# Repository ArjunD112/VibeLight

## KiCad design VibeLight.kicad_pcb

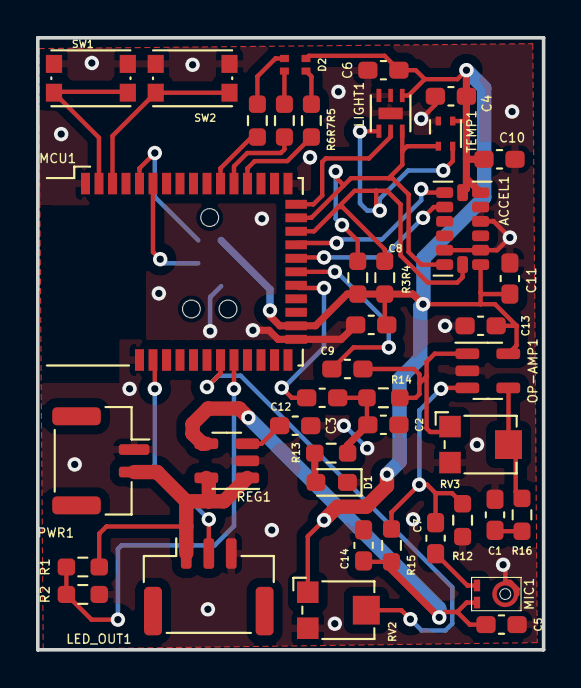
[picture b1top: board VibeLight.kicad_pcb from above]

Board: 2 copper layers, 28.1 x 34.0 mm, 42 parts (1 on the bottom side), 31 nets.

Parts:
ACCEL1: ADXL343; LGA-14_3x5mm_P0.8mm_LayoutBorder1x6y
C1, C5, C9, C12, C13, C14: 100 nF; C_0603_1608Metric_Pad1.08x0.95mm_HandSolder
C2, C7, C10: 1 uF; C_0603_1608Metric_Pad1.08x0.95mm_HandSolder
C3, C4, C6, C8, C11: 100nF; C_0603_1608Metric_Pad1.08x0.95mm_HandSolder
D1: LED; LED_0603_1608Metric_Pad1.05x0.95mm_HandSolder
D2: LED_RBAG; LED_APHB1608LZGKSURKC
J1: Conn_ARM_SWD_TagConnect_TC2030-NL; Tag-Connect_TC2030-IDC-NL_2x03_P1.27mm_Vertical
LED_OUT1: Conn_01x03_Pin; JST_GH_SM03B-GHS-TB_1x03-1MP_P1.25mm_Horizontal
LIGHT1: OPT3002-ALS; SON65P200X200X65-7N
MCU1: BL652; Laird_BL652
MIC1: SPV08A0LR5H-1
OP-AMP1: AD8603; TSOT-23-5
PWR1: Conn_01x02; JST_GH_SM02B-GHS-TB_1x02-1MP_P1.25mm_Horizontal
R1, R2: 100K; R_0603_1608Metric_Pad0.98x0.95mm_HandSolder
R3, R4: 4.7K; R_0603_1608Metric_Pad0.98x0.95mm_HandSolder
R5, R6, R7, R13: 100R; R_0603_1608Metric_Pad0.98x0.95mm_HandSolder
R12, R15, R16: 10K; R_0603_1608Metric_Pad0.98x0.95mm_HandSolder
R14: 620R; R_0603_1608Metric_Pad0.98x0.95mm_HandSolder
REG1: LK112M33TR; SOT-23-5
RV2: Intensity Dial; Potentiometer_Bourns_TC33X_Vertical
RV3: Sens Dial; Potentiometer_Bourns_TC33X_Vertical
SW1, SW2: SW_Push; SW_Push_1P1T_NO_CK_KMR2
TEMP1: SHT4x; Sensirion_DFN-4_1.5x1.5mm_P0.8mm_SHT4x_NoCentralPad

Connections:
+3V3: ACCEL1.1 (Vdd_I/O), ACCEL1.6 (Vs), ACCEL1.7 (~CS), C4.1, C5.2, C6.1, C8.1, C10.1, C11.1, C13.2, C14.2, D2.3 (A), J1.1 (VCC), LIGHT1.1 (VDD), MCU1.26 (VDD), MIC1.VDDA, OP-AMP1.5 (V+), R3.2, R4.2, R15.1, REG1.4 (OUT), RV2.1, TEMP1.3 (VDD)
/Audio Input/FIL: C12.2, MCU1.23 (SIO_02/AIN0)
/Audio Input/MEMS Mic/2_OUT: C7.2, MIC1.OUT
/Audio Input/RAW: C9.2, MCU1.22 (SIO_03/AIN1)
/BATT+: LED_OUT1.1, PWR1.2, R1.1, REG1.1 (SHDN), REG1.5 (IN)
/CNTRL: LED_OUT1.2, MCU1.38 (SIO_25)
/MCU/ACC_INT1: ACCEL1.8 (INT1), MCU1.20 (SIO_05/AIN3)
/MCU/ACC_INT2: ACCEL1.9 (INT2), MCU1.21 (SIO_04/AIN2)
/MCU/Intensity_Dial: MCU1.33 (SIO_30/AIN6), RV2.2
/MCU/OPT_INT: LIGHT1.5 (INT), MCU1.17 (SIO_08)
/MCU/SW1: MCU1.2 (SIO_24), SW1.1
/MCU/SW2: MCU1.3 (SIO_23), SW2.1
/MCU/SWCLK: J1.4 (SWCLK), MCU1.6 (SWDCLK)
/MCU/SWDIO: J1.2 (SWDIO), MCU1.5 (SWDIO)
/SCL: ACCEL1.14 (SCL/SCLK), LIGHT1.4 (SCL), MCU1.19 (SIO_06), R4.1, TEMP1.2 (SCL)
/SDA: ACCEL1.13 (SDA/SDI/SDIO), LIGHT1.6 (SDA), MCU1.18 (SIO_07), R3.1, TEMP1.1 (SDA)
GND: ACCEL1.2 (GND), ACCEL1.4 (GND), ACCEL1.5 (GND), ACCEL1.12 (SDO/ADDR), C1.1, C2.1, C3.2, C4.2, C5.1, C6.2, C8.2, C10.2, C11.2, C13.1, C14.1, D1.1 (K), J1.5 (GND), LED_OUT1.3, LIGHT1.2 (ADDR), LIGHT1.3 (GND), LIGHT1.7, MCU1.1 (GND), MCU1.16 (GND), MCU1.27 (GND), MCU1.39 (GND), MIC1.AGND, OP-AMP1.2 (V-), PWR1.1, R2.2, R12.2, REG1.2 (GND), RV2.3, RV3.3, SW1.2, SW2.2, TEMP1.4 (VSS)
unnamed: C1.2, R16.2
unnamed: C9.1, OP-AMP1.1, R14.1, RV3.1
unnamed: C2.2, C12.1, R13.1, R14.2
unnamed: D1.2 (A), R13.2
unnamed: D2.2 (BK), R7.2
unnamed: D2.4 (GK), R6.1
unnamed: D2.1 (RK), R5.1
unnamed: MCU1.13 (SIO_11), R5.2
unnamed: MCU1.12 (SIO_12), R7.1
unnamed: MCU1.11 (SIO_14), R6.2
unnamed: MCU1.32 (SIO_31/AIN7), R1.2, R2.1
unnamed: C7.1, OP-AMP1.3 (+), R12.1, R15.2
unnamed: OP-AMP1.4 (-), R16.1, RV3.2
unnamed: C3.1, REG1.3 (Bypass)

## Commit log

2023-07-31 Rev 1
    needs sensors, things like pull-up resistors and protection diodes, electrical rules check. also check SCL and SDA busses, variable resistors
2023-07-31 added debug LED after Op-Amp
    want battery status LED?
2023-08-01 added some components
2023-08-01 misc changes during call
2023-08-02 started work on pcb layout
    started work on pcb layout
2023-08-02 added OPT and JST footprints
2023-08-03 completed rev1 of PCB layout
    need to double check components and other elements, connections, and add values
2023-08-03 Changes from DR call
2023-08-04 pcB rev2
    need to fix reference texts on PCB, figure out MEMs mic wiring
2023-08-04 slight layout changes, nothing big
2023-08-04 updates from call
2023-08-05 new pcb rev with updated audio filter
    The only ERC and DRC warnings/errors are unconnected pins and silkscreen text issues. There are two DRC issues that have to do with the mic, but I don't think they're an issue
2023-08-05 cleaned up unused footprint files
2023-08-05 Misc updates and tweak. Work still needed, letf notes in top schematic page
2023-08-05 update
    updated in accordance with 8/5 schem notes
2023-08-07 updated GND vias and unconnected errors
2023-08-08 R1 Release package
2023-08-08 updated resistor value in audio filter
2023-08-09 added BOM file
